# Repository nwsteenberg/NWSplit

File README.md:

# NWSplit

> A 52-key, column-staggered split ergonomic keyboard developed almost entirely through **Ergogen**.

The goal: build the *perfect* keyboard for me. Of course, getting there meant going through a handful of prototypes that didn't quite make the cut. Take a look at the [Graveyard](images/graveyard) to see the keyboards that didn't make the cut.

---

## ✨ Features
* **Declarative:** Designed in [Ergogen](https://ergogen.xyz/) (both case and PCB).
* **Firmware:** Powered by **QMK & VIAL** for real-time keymap customization without flashing.
* **Choc Switches:** Hot-swap support for Kailh Choc v1 and v2 switches.
* **Per-Key RGB:** SK6812 MINI-E lighting support.
* **Extra Inputs:** Optional rotary encoder support (up to 2).

---

## 📂 Repository Structure

* `3d/` — 3D printable models (`.stl`) for the keyboard and expansion modules.
* `firmware/` — Vial/QMK firmware source files and layouts.
* `footprints/` — Custom Ergogen and KiCad footprints.
* `images/` — Renders, wiring diagrams, and build photos.
* `production/` — Ready-to-use PCB production files (Gerbers).
* `traced-pcbs/` — Autogenerated and manually traced KiCad PCB projects.
* `keyboard.yaml` — Ergogen configuration file for the main keyboard.
* `expansion.yaml` — Ergogen configuration file for the expansion modules.

---

## 🛒 Bill of Materials (BOM)

| Component | Description | Quantity | Notes |
| :--- | :--- | :---: | :--- |
| **PCB** | Gerber available in `production/` | 2 | Reversible (left and right use the exact same PCB) |
| **Diodes** | 1N4148, SOD123 | 52 | |
| **MCU** | Waveshare RP2040-Zero | 2 | Clones work too just verify pinout compatibility |
| **TRRS Connector** | PJ320A Jack | 2 | |
| **Switches** | Kailh Choc V1/V2 | 52 | Dont use V2 with guide pin (stock red/blue/brown) |
| **Keycaps** | Low-profile keycaps of choice | 52 | THT or LPF profiles recommended |
| **Heat Inserts** | M2 L3 OD3.5 (or OD3 for resin prints) | 12 | |
| **Per-Key LEDs** | SK6812 MINI-E | 52 | *Optional* |
| **Rotary Encoder** | EC11 / EC12 | 0–2 | *Optional* (supports button click) |
| **Pogo Connectors** | Angled 6-pin Magnetic Pogo Pins | 0–2 | *Optional* (used for experimental modular connections) |

---

## 🚀 Roadmap & TODO

- [ ] **Build Instructions:** Step-by-step assembly guide.
- [ ] **Sandwitch case:** Cheap case option without 3d printing.
- [ ] **Expansion Modules:** 
  - [x] Trackball
  - [x] Trackpad
- [ ] **Images:** Add build process and final images of the keyboard and expansions.
- [ ] **Graveyard:** Show what keyboards didn't make the cut.

---

## 💡 Inspiration

Throughout the journey the following projects provided a ton of inspiration to create the version of the keyboard as it is today:
* [christianselig/caldera](https://christianselig.com/2024/07/caldera-keyboard/)
* [achyudh/karma](https://github.com/achyudh/karma)
* [carrefinho/forager](https://github.com/carrefinho/forager)

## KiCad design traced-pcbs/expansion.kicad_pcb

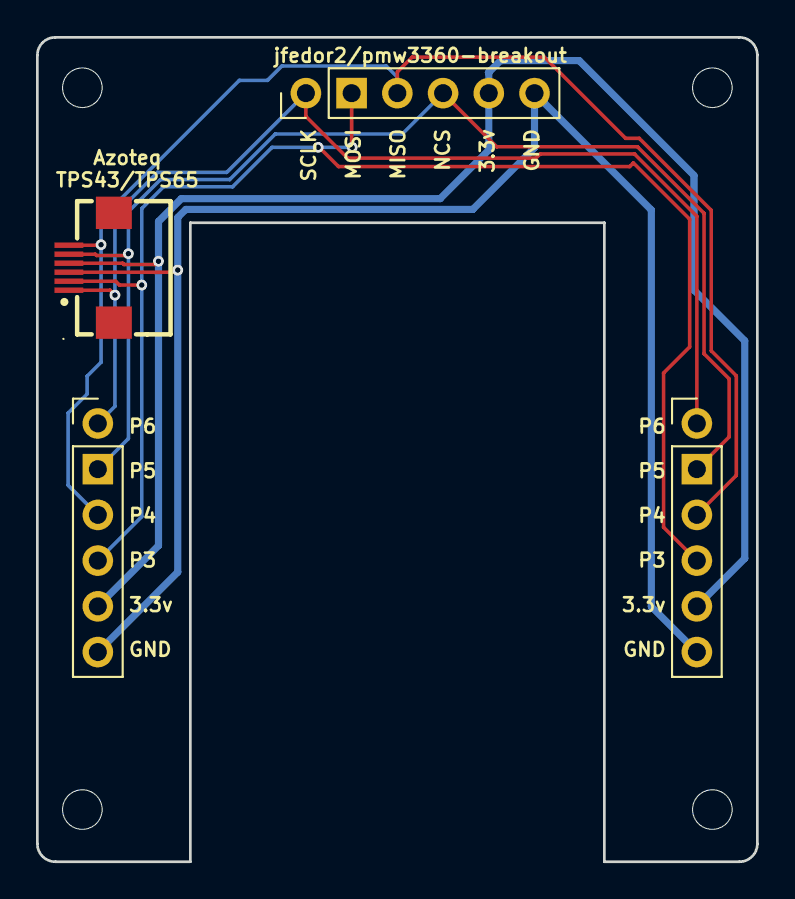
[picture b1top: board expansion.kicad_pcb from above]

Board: 2 copper layers, 40.0 x 45.8 mm, 8 parts (0 on the bottom side), 6 nets.

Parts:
C1: FPC-SMD_FPC05006-09200
MH1, MH2, MH3, MH4: mounting_hole_npth
Pin Header 2.54 1x61, Pin Header 2.54 1x62, Pin Header 2.54 1x63: PinHeader_1x06_P2.54mm_Vertical

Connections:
GND: C1.3, Pin Header 2.54 1x61.6, Pin Header 2.54 1x62.6, Pin Header 2.54 1x63.6
P1: C1.1, Pin Header 2.54 1x61.1, Pin Header 2.54 1x62.1, Pin Header 2.54 1x63.1
P2: C1.5, Pin Header 2.54 1x61.2, Pin Header 2.54 1x62.2, Pin Header 2.54 1x63.4
P3: C1.6, Pin Header 2.54 1x61.3, Pin Header 2.54 1x62.3, Pin Header 2.54 1x63.3
P3V3: C1.4, Pin Header 2.54 1x61.5, Pin Header 2.54 1x62.5, Pin Header 2.54 1x63.5
P4: C1.2, Pin Header 2.54 1x61.4, Pin Header 2.54 1x62.4, Pin Header 2.54 1x63.2

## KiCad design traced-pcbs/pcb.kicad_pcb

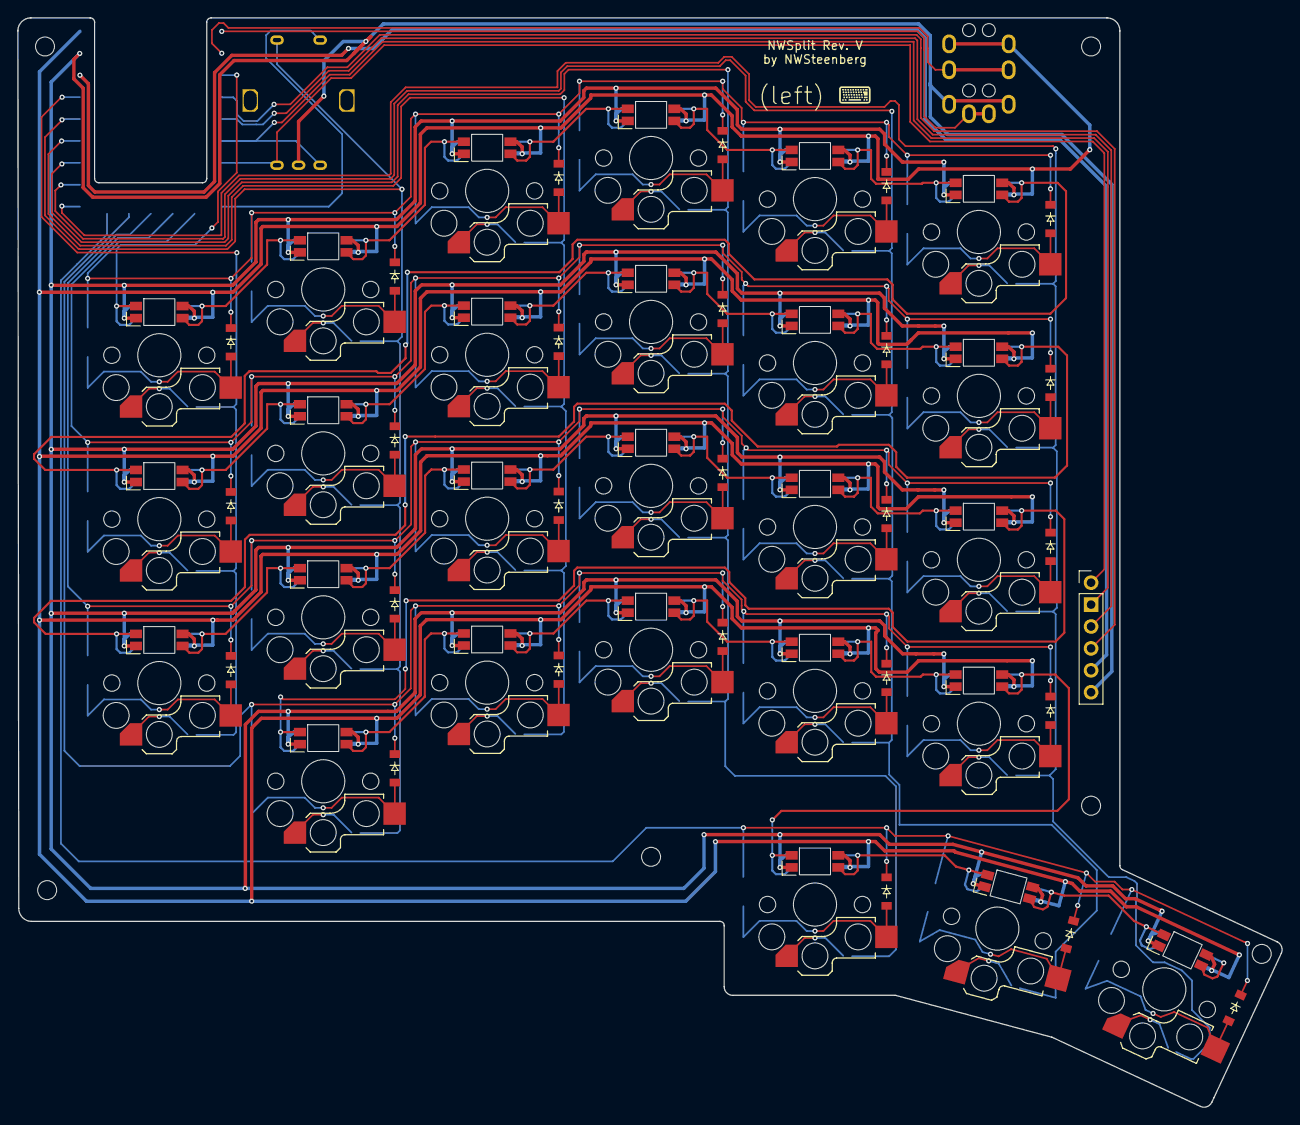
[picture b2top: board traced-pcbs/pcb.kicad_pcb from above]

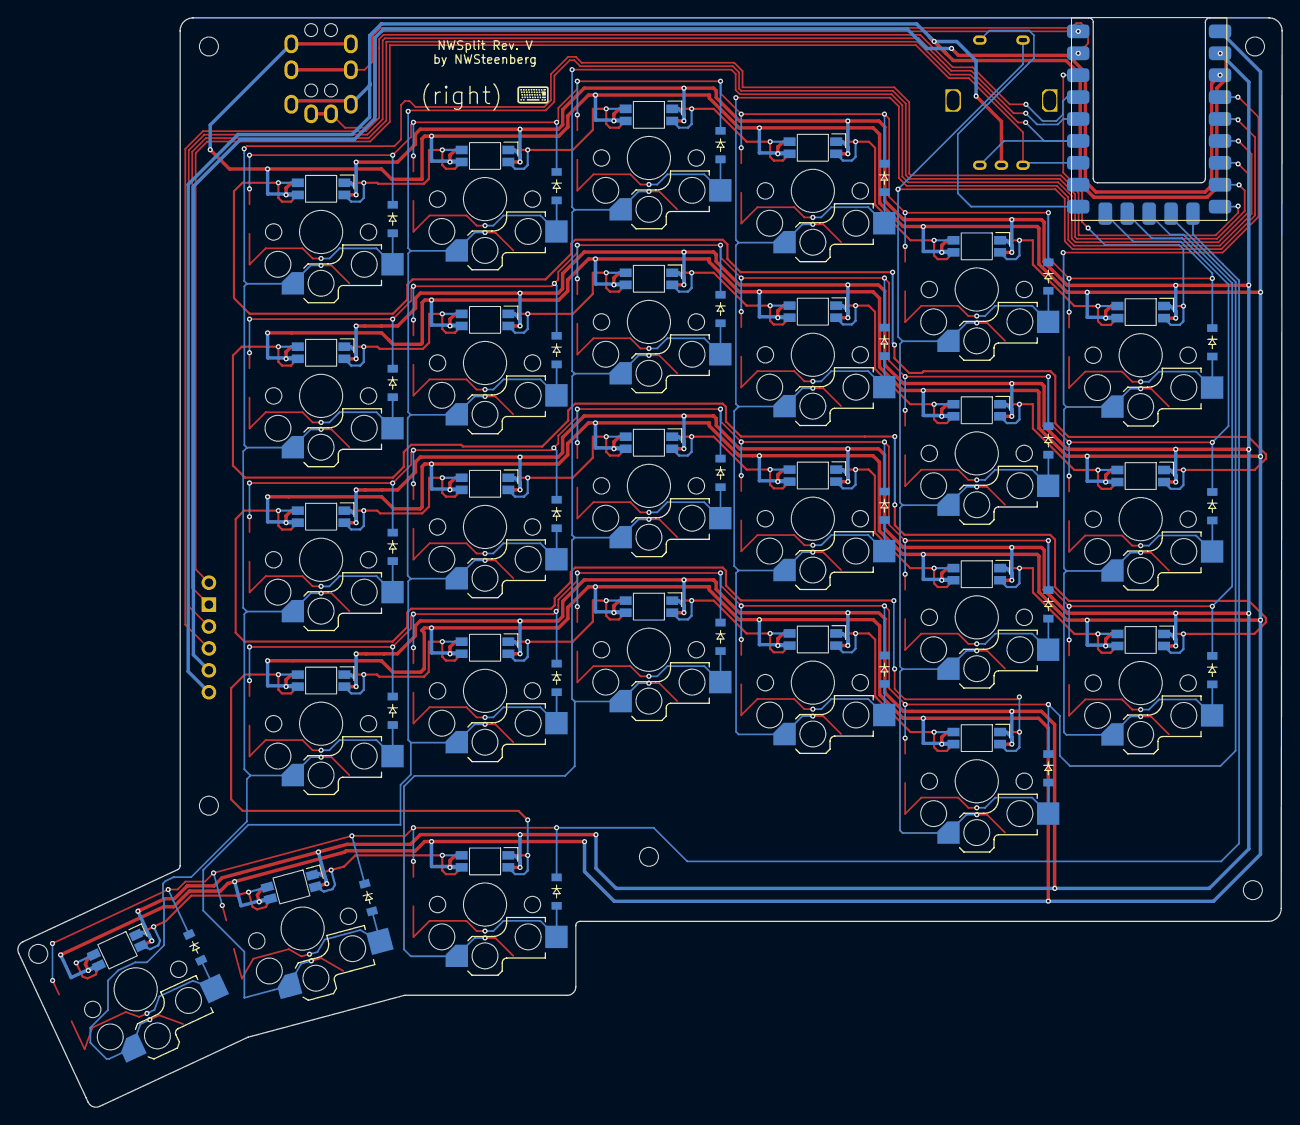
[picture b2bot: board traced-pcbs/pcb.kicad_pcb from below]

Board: 2 copper layers, 146.5 x 126.3 mm, 113 parts (78 on the bottom side), 42 nets.

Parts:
D1, D2, D3, D4, D5, D6, D7, D8, D9, D10, D11, D12, D13, D14, D15, D16, D17, D18, D19, D20, D21, D22, D23, D24, D25, D26, D27, D28, D29, D30, D31, D32, D33, D34, D35, D36, D37, D38, D39, D40, D41, D42, D43, D44, D45, D46, D47, D48, D49, D50, D51, D52: diode_tht_sod123
LED1, LED2, LED3, LED4, LED5, LED6, LED7, LED8, LED9, LED10, LED11, LED12, LED13, LED14, LED15, LED16, LED17, LED18, LED19, LED20, LED21, LED22, LED23, LED24, LED25, LED26: led_SK6812mini-e (per-key, reversible)
MH1, MH2, MH3, MH4, MH5, MH6: mounting_hole_npth
Pin Header 2.54 1x61: PinHeader_1x06_P2.54mm_Vertical
RE1: rotary_encoder_ec11_ec12
S1, S2, S3, S4, S5, S6, S7, S8, S9, S10, S11, S12, S13, S14, S15, S16, S17, S18, S19, S20, S21, S22, S23, S24, S25, S26: switch_choc_v1_v2
TRRS1: trrs_pj320a (reversible)

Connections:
GND: LED1.3, LED2.3, LED3.3, LED4.3, LED5.3, LED6.3, LED7.3, LED8.3, LED9.3, LED10.3, LED11.3, LED12.3, LED13.3, LED14.3, LED15.3, LED16.3, LED17.3, LED18.3, LED19.3, LED20.3, LED21.3, LED22.3, LED23.3, LED24.3, LED25.3, LED26.3, Pin Header 2.54 1x61.6, RE1.B, TRRS1.4
GP5: Pin Header 2.54 1x61.2, RE1.A
GP6: Pin Header 2.54 1x61.1, RE1.C
GP9: D3.1, D7.1, D11.1, D15.1, D19.1, D23.1, D29.1, D33.1, D37.1, D41.1, D45.1, D49.1
GP10: D2.1, D6.1, D10.1, D14.1, D18.1, D22.1, D28.1, D32.1, D36.1, D40.1, D44.1, D48.1
GP11: D1.1, D5.1, D9.1, D13.1, D17.1, D21.1, D27.1, D31.1, D35.1, D39.1, D43.1, D47.1
GP12: D4.1, D8.1, D12.1, D16.1, D20.1, D30.1, D34.1, D38.1, D42.1, D46.1
GP13: D24.1, D25.1, D26.1, D50.1, D51.1, D52.1
GP14: S20.1, S21.1, S22.1, S23.1, S26.1
GP15: S16.1, S17.1, S18.1, S19.1, S25.1
GP26: S12.1, S13.1, S14.1, S15.1, S24.1
GP27: S8.1, S9.1, S10.1, S11.1
GP28: RE1.S1, S4.1, S5.1, S6.1, S7.1
GP29: S1.1, S2.1, S3.1
LED_NET: LED1.2, LED2.2, LED2.4, LED3.2, LED3.4, LED4.2, LED4.4, LED5.2, LED5.4, LED6.2, LED6.4, LED7.2, LED7.4, LED8.2, LED8.4, LED9.2, LED9.4, LED10.2, LED10.4, LED11.2, LED11.4, LED12.2, LED12.4, LED13.2, LED13.4, LED14.2, LED14.4, LED15.2, LED15.4, LED16.2, LED16.4, LED17.2, LED17.4, LED18.2, LED18.4, LED19.2, LED19.4, LED20.2, LED20.4, LED21.2, LED21.4, LED22.2, LED22.4, LED23.2, LED23.4, LED24.2, LED24.4, LED25.2, LED25.4, LED26.2, LED26.4
P5V: LED1.1, LED2.1, LED3.1, LED4.1, LED5.1, LED6.1, LED7.1, LED8.1, LED9.1, LED10.1, LED11.1, LED12.1, LED13.1, LED14.1, LED15.1, LED16.1, LED17.1, LED18.1, LED19.1, LED20.1, LED21.1, LED22.1, LED23.1, LED24.1, LED25.1, LED26.1, TRRS1.2
center_only: D25.2, D51.2, S25.2
index_bottom: D16.2, D42.2, S16.2
index_home: D17.2, D43.2, S17.2
index_num: D19.2, D45.2, S19.2
index_top: D18.2, D44.2, S18.2
inner_bottom: D20.2, D46.2, S20.2
inner_home: D21.2, D47.2, S21.2
inner_num: D23.2, D49.2, S23.2
inner_only: D24.2, D50.2, S24.2
inner_top: D22.2, D48.2, S22.2
middle_bottom: D12.2, D38.2, S12.2
middle_home: D13.2, D39.2, S13.2
middle_num: D15.2, D41.2, S15.2
middle_top: D14.2, D40.2, S14.2
outer_home: D1.2, D27.2, S1.2
outer_num: D3.2, D29.2, S3.2
outer_only: D26.2, D52.2, S26.2
outer_top: D2.2, D28.2, S2.2
pinky_bottom: D4.2, D30.2, S4.2
pinky_home: D5.2, D31.2, S5.2
pinky_num: D7.2, D33.2, S7.2
pinky_top: D6.2, D32.2, S6.2
ring_bottom: D8.2, D34.2, S8.2
ring_home: D9.2, D35.2, S9.2
ring_num: D11.2, D37.2, S11.2
ring_top: D10.2, D36.2, S10.2

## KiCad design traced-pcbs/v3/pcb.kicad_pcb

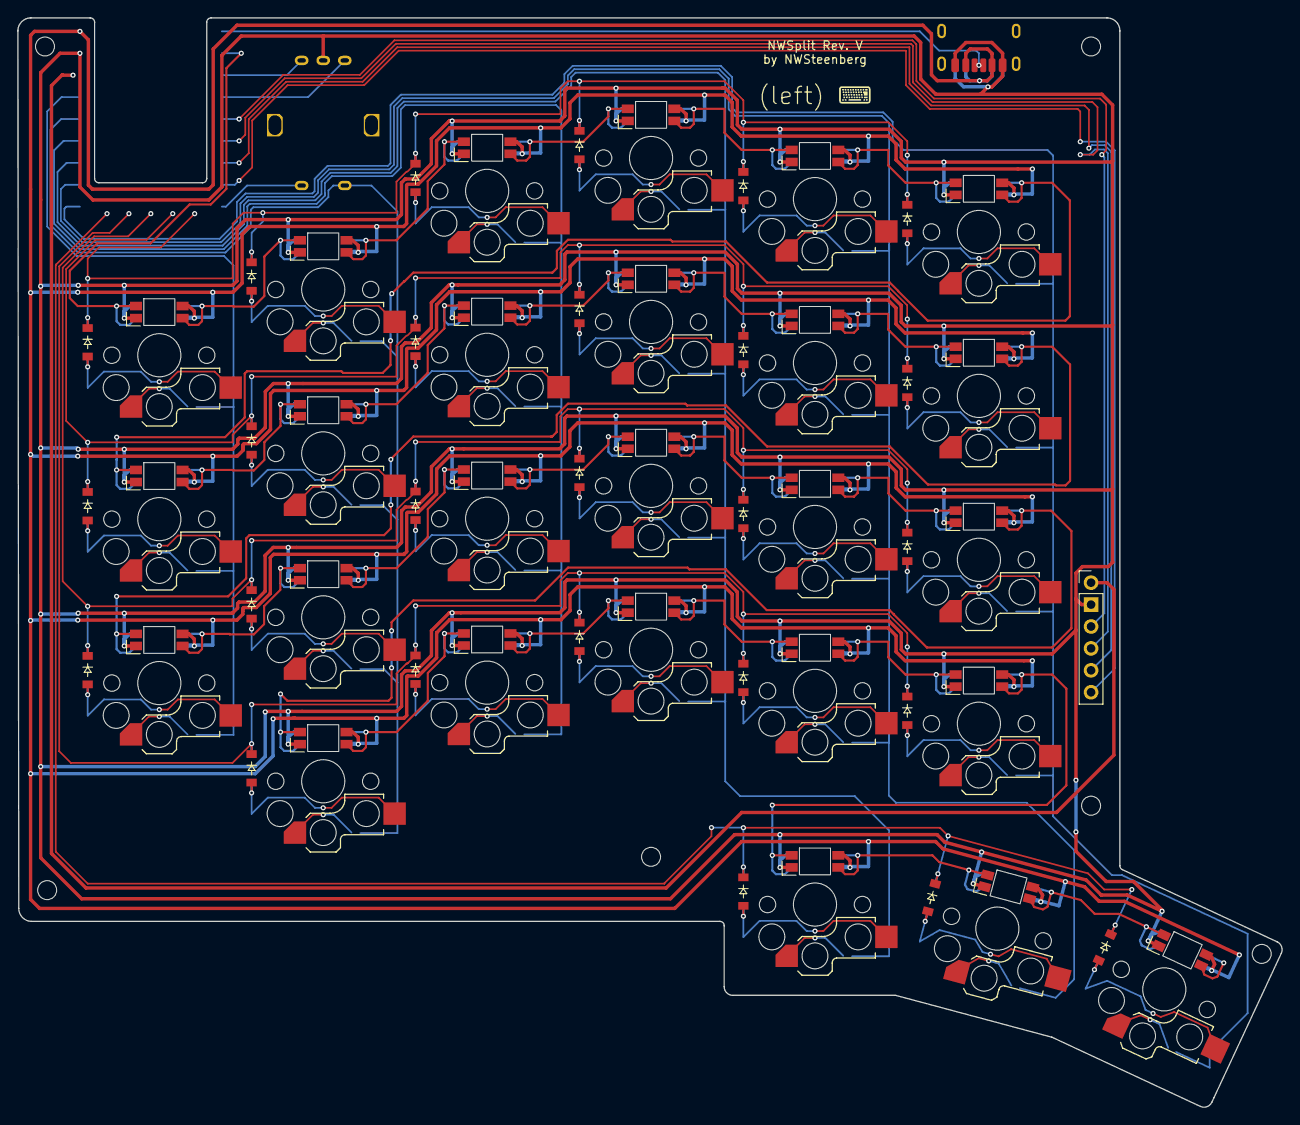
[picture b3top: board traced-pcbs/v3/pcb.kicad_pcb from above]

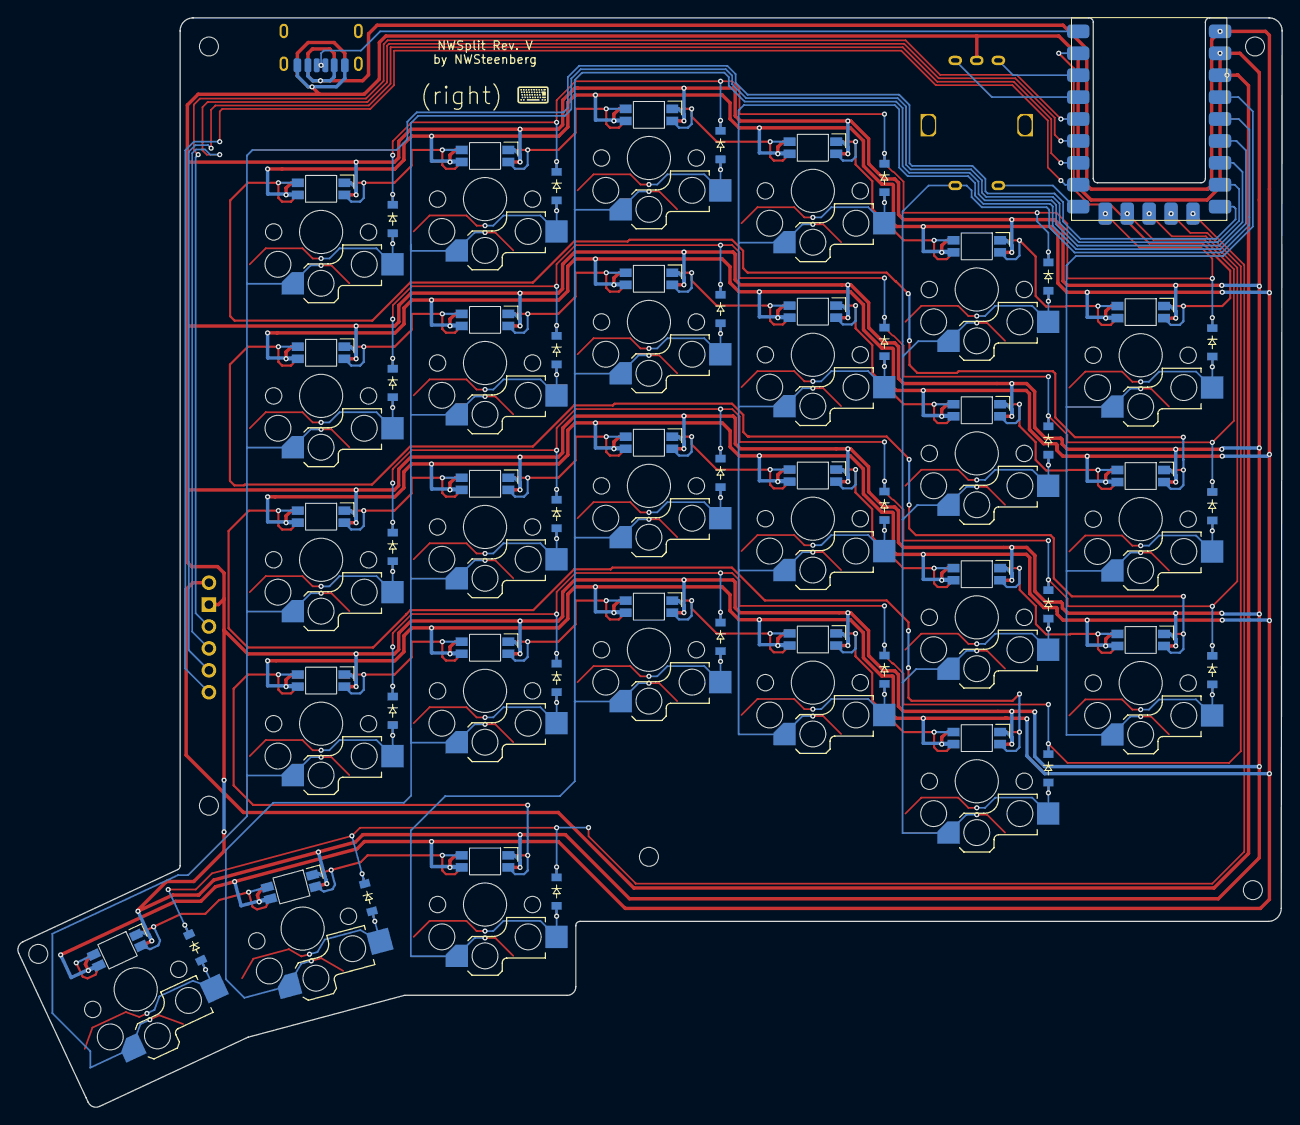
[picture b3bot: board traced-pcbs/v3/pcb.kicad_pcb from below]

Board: 2 copper layers, 146.5 x 126.3 mm, 87 parts (52 on the bottom side), 41 nets.

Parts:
D1, D2, D3, D4, D5, D6, D7, D8, D9, D10, D11, D12, D13, D14, D15, D16, D17, D18, D19, D20, D21, D22, D23, D24, D25, D26: diode_tht_sod123
LED1, LED2, LED3, LED4, LED5, LED6, LED7, LED8, LED9, LED10, LED11, LED12, LED13, LED14, LED15, LED16, LED17, LED18, LED19, LED20, LED21, LED22, LED23, LED24, LED25, LED26: led_SK6812mini-e (per-key, reversible)
MH1, MH2, MH3, MH4, MH5, MH6: mounting_hole_npth
Pin Header 2.54 1x61: PinHeader_1x06_P2.54mm_Vertical
RE1: rotary_encoder_ec11_ec12
S1, S2, S3, S4, S5, S6, S7, S8, S9, S10, S11, S12, S13, S14, S15, S16, S17, S18, S19, S20, S21, S22, S23, S24, S25, S26: switch_choc_v1_v2
USB-C 6 Pin Recepticle1: USB_C_Receptacle_HRO_TYPE-C-31-M-17

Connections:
GND: LED1.3, LED2.3, LED3.3, LED4.3, LED5.3, LED6.3, LED7.3, LED8.3, LED9.3, LED10.3, LED11.3, LED12.3, LED13.3, LED14.3, LED15.3, LED16.3, LED17.3, LED18.3, LED19.3, LED20.3, LED21.3, LED22.3, LED23.3, LED24.3, LED25.3, LED26.3, Pin Header 2.54 1x61.2, RE1.B, USB-C 6 Pin Recepticle1.A12, USB-C 6 Pin Recepticle1.B12
GP9: D3.1, D7.1, D11.1, D15.1, D19.1, D23.1
GP10: D2.1, D6.1, D10.1, D14.1, D18.1, D22.1
GP11: D1.1, D5.1, D9.1, D13.1, D17.1, D21.1
GP12: D4.1, D8.1, D12.1, D16.1, D20.1
GP13: D24.1, D25.1, D26.1
GP14: S20.1, S21.1, S22.1, S23.1, S26.1
GP15: S16.1, S17.1, S18.1, S19.1, S25.1
GP26: S12.1, S13.1, S14.1, S15.1, S24.1
GP27: S8.1, S9.1, S10.1, S11.1
GP28: RE1.S1, S4.1, S5.1, S6.1, S7.1
GP29: S1.1, S2.1, S3.1
LED_NET: LED1.2, LED2.2, LED2.4, LED3.2, LED3.4, LED4.2, LED4.4, LED5.2, LED5.4, LED6.2, LED6.4, LED7.2, LED7.4, LED8.2, LED8.4, LED9.2, LED9.4, LED10.2, LED10.4, LED11.2, LED11.4, LED12.2, LED12.4, LED13.2, LED13.4, LED14.2, LED14.4, LED15.2, LED15.4, LED16.2, LED16.4, LED17.2, LED17.4, LED18.2, LED18.4, LED19.2, LED19.4, LED20.2, LED20.4, LED21.2, LED21.4, LED22.2, LED22.4, LED23.2, LED23.4, LED24.2, LED24.4, LED25.2, LED25.4, LED26.2, LED26.4
P5V: LED1.1, LED2.1, LED3.1, LED4.1, LED5.1, LED6.1, LED7.1, LED8.1, LED9.1, LED10.1, LED11.1, LED12.1, LED13.1, LED14.1, LED15.1, LED16.1, LED17.1, LED18.1, LED19.1, LED20.1, LED21.1, LED22.1, LED23.1, LED24.1, LED25.1, LED26.1, USB-C 6 Pin Recepticle1.A9, USB-C 6 Pin Recepticle1.B9
SERIAL_DATA: USB-C 6 Pin Recepticle1.A5, USB-C 6 Pin Recepticle1.B5
center_only: D25.2, S25.2
index_bottom: D16.2, S16.2
index_home: D17.2, S17.2
index_num: D19.2, S19.2
index_top: D18.2, S18.2
inner_bottom: D20.2, S20.2
inner_home: D21.2, S21.2
inner_num: D23.2, S23.2
inner_only: D24.2, S24.2
inner_top: D22.2, S22.2
middle_bottom: D12.2, S12.2
middle_home: D13.2, S13.2
middle_num: D15.2, S15.2
middle_top: D14.2, S14.2
outer_home: D1.2, S1.2
outer_num: D3.2, S3.2
outer_only: D26.2, S26.2
outer_top: D2.2, S2.2
pinky_bottom: D4.2, S4.2
pinky_home: D5.2, S5.2
pinky_num: D7.2, S7.2
pinky_top: D6.2, S6.2
ring_bottom: D8.2, S8.2
ring_home: D9.2, S9.2
ring_num: D11.2, S11.2
ring_top: D10.2, S10.2

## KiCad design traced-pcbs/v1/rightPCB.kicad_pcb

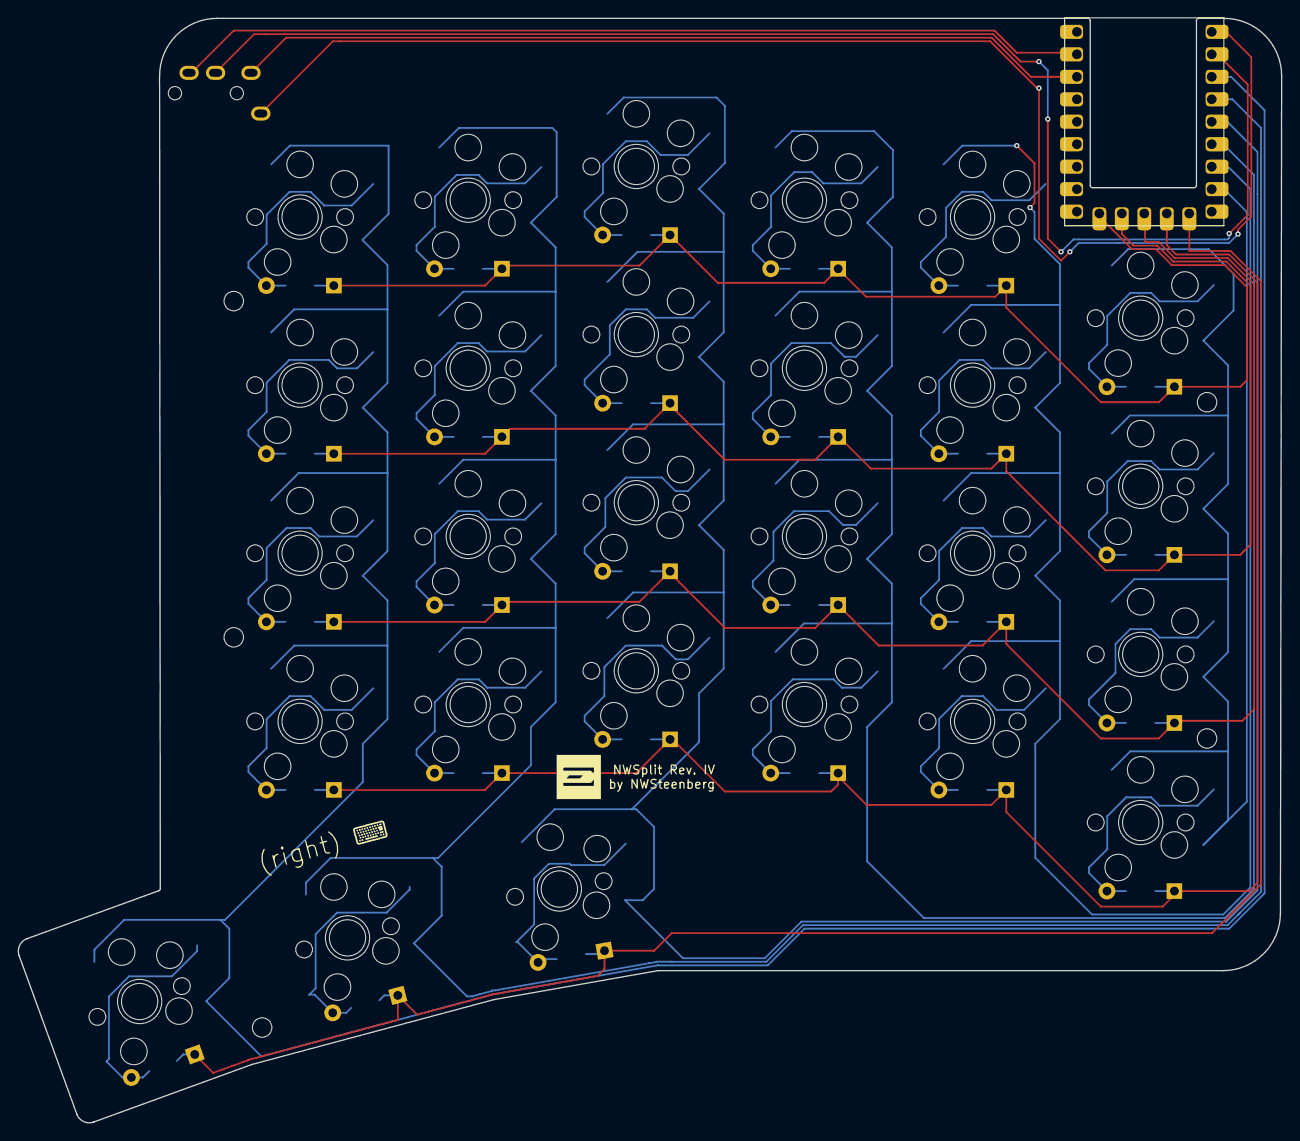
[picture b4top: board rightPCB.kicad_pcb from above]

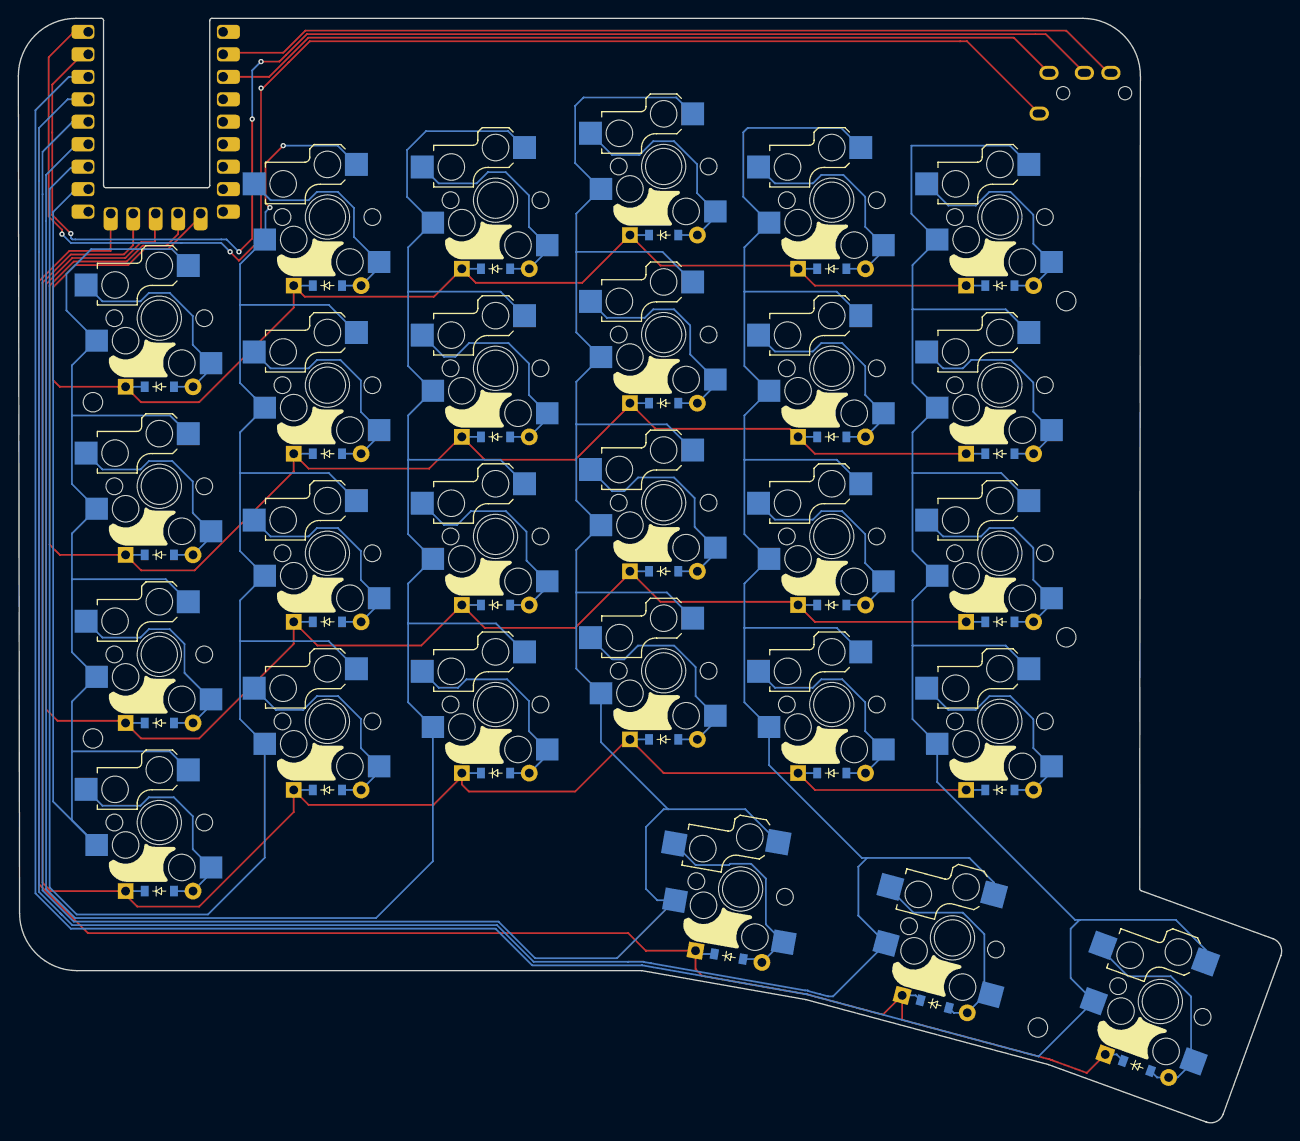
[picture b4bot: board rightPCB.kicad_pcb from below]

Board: 2 copper layers, 142.8 x 124.8 mm, 89 parts (81 on the bottom side), 42 nets.

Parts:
D1, D2, D3, D4, D5, D6, D7, D8, D9, D10, D11, D12, D13, D14, D15, D16, D17, D18, D19, D20, D21, D22, D23, D24, D25, D26, D27: diode_tht_sod123
LOGO1: utility_ergogen_logo
MH1, MH2, MH3, MH4, MH5: mounting_hole_npth
RP2040-Zero: RP2040-Zero
S1, S2, S3, S4, S5, S6, S7, S8, S9, S10, S11, S12, S13, S14, S15, S16, S17, S18, S19, S20, S21, S22, S23, S24, S25, S26, S27: switch_choc_v1_v2
S28, S29, S30, S31, S32, S33, S34, S35, S36, S37, S38, S39, S40, S41, S42, S43, S44, S45, S46, S47, S48, S49, S50, S51, S52, S53, S54: switch_mx
TRRS1: trrs_pj320a

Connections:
GND: RP2040-Zero.20, TRRS1.2
GP0: RP2040-Zero.1, TRRS1.5
GP1: RP2040-Zero.2, TRRS1.3
GP2: RP2040-Zero.3, S21.1, S22.1, S23.1, S24.1, S27.1, S48.1, S49.1, S50.1, S51.1, S54.1
GP3: RP2040-Zero.4, S17.1, S18.1, S19.1, S20.1, S26.1, S44.1, S45.1, S46.1, S47.1, S53.1
GP4: RP2040-Zero.5, S13.1, S14.1, S15.1, S16.1, S25.1, S40.1, S41.1, S42.1, S43.1, S52.1
GP5: RP2040-Zero.6, S9.1, S10.1, S11.1, S12.1, S36.1, S37.1, S38.1, S39.1
GP6: RP2040-Zero.7, S5.1, S6.1, S7.1, S8.1, S32.1, S33.1, S34.1, S35.1
GP7: RP2040-Zero.8, S1.1, S2.1, S3.1, S4.1, S28.1, S29.1, S30.1, S31.1
GP9: D25.1, D26.1, D27.1, RP2040-Zero.10
GP10: D1.1, D5.1, D9.1, D13.1, D17.1, D21.1, RP2040-Zero.11
GP11: D2.1, D6.1, D10.1, D14.1, D18.1, D22.1, RP2040-Zero.12
GP12: D3.1, D7.1, D11.1, D15.1, D19.1, D23.1, RP2040-Zero.13
GP13: D4.1, D8.1, D12.1, D16.1, D20.1, D24.1, RP2040-Zero.14
P3V3: RP2040-Zero.21, TRRS1.4
mirror_center_only: D26.2, S26.2, S53.2
mirror_index_bottom: D17.2, S17.2, S44.2
mirror_index_home: D18.2, S18.2, S45.2
mirror_index_num: D20.2, S20.2, S47.2
mirror_index_top: D19.2, S19.2, S46.2
mirror_inner_bottom: D21.2, S21.2, S48.2
mirror_inner_home: D22.2, S22.2, S49.2
mirror_inner_num: D24.2, S24.2, S51.2
mirror_inner_only: D25.2, S25.2, S52.2
mirror_inner_top: D23.2, S23.2, S50.2
mirror_middle_bottom: D13.2, S13.2, S40.2
mirror_middle_home: D14.2, S14.2, S41.2
mirror_middle_num: D16.2, S16.2, S43.2
mirror_middle_top: D15.2, S15.2, S42.2
mirror_outer_bottom: D1.2, S1.2, S28.2
mirror_outer_home: D2.2, S2.2, S29.2
mirror_outer_num: D4.2, S4.2, S31.2
mirror_outer_top: D3.2, S3.2, S30.2
mirror_pinky_bottom: D5.2, S5.2, S32.2
mirror_pinky_home: D6.2, S6.2, S33.2
mirror_pinky_num: D8.2, S8.2, S35.2
mirror_pinky_top: D7.2, S7.2, S34.2
mirror_reach_only: D27.2, S27.2, S54.2
mirror_ring_bottom: D9.2, S9.2, S36.2
mirror_ring_home: D10.2, S10.2, S37.2
mirror_ring_num: D12.2, S12.2, S39.2
mirror_ring_top: D11.2, S11.2, S38.2

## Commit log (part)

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2026-01-27 First iteration of keyboard
2026-02-05 Updated after case changes
2026-02-13 Fixed vial-qmk
2026-02-16 Added images
2026-03-02 [CASE] * Changed baseheight to 1 * Removed wallAroundKeys * Remove material at thumb buttons
2026-03-31 Updated case: * bigger platform for pcb * standoffs for bottom (heated inserts)
2026-03-31 Updated case using ergogen
2026-04-01 Cleaned up repo and setup artifacts for github-actions. Added initial ergogen action
2026-04-01 Add ceoloide ergogen-footprints as submodule
2026-04-01 Updated actions
2026-04-03 Added vial setup
2026-06-20 Initial v2 commit * Add all v1 resources into specific folders * Remove waveshare-rp2040 - never used * updated rp2040zero footprint * added v2 config
2026-06-20 Now buildds actions on branches
2026-06-20 Added some trace helpers
2026-06-21 Updated config with more flair
2026-06-25 Reworked case and pcb to fit usb breakout instead of trrs
2026-06-28 Added lighting and moved stuff around
2026-06-28 Fixed QMK errors
2026-06-28 Fixes to keyboard.json
2026-06-28 Fixes
2026-06-28 Remove split rgb flag
2026-06-28 remove legacy rgblight
2026-06-28 Specify vendor driver for ws2812
2026-06-30 Updated coords for rgb matrix and layout
2026-06-30 Aligned ergogen config
